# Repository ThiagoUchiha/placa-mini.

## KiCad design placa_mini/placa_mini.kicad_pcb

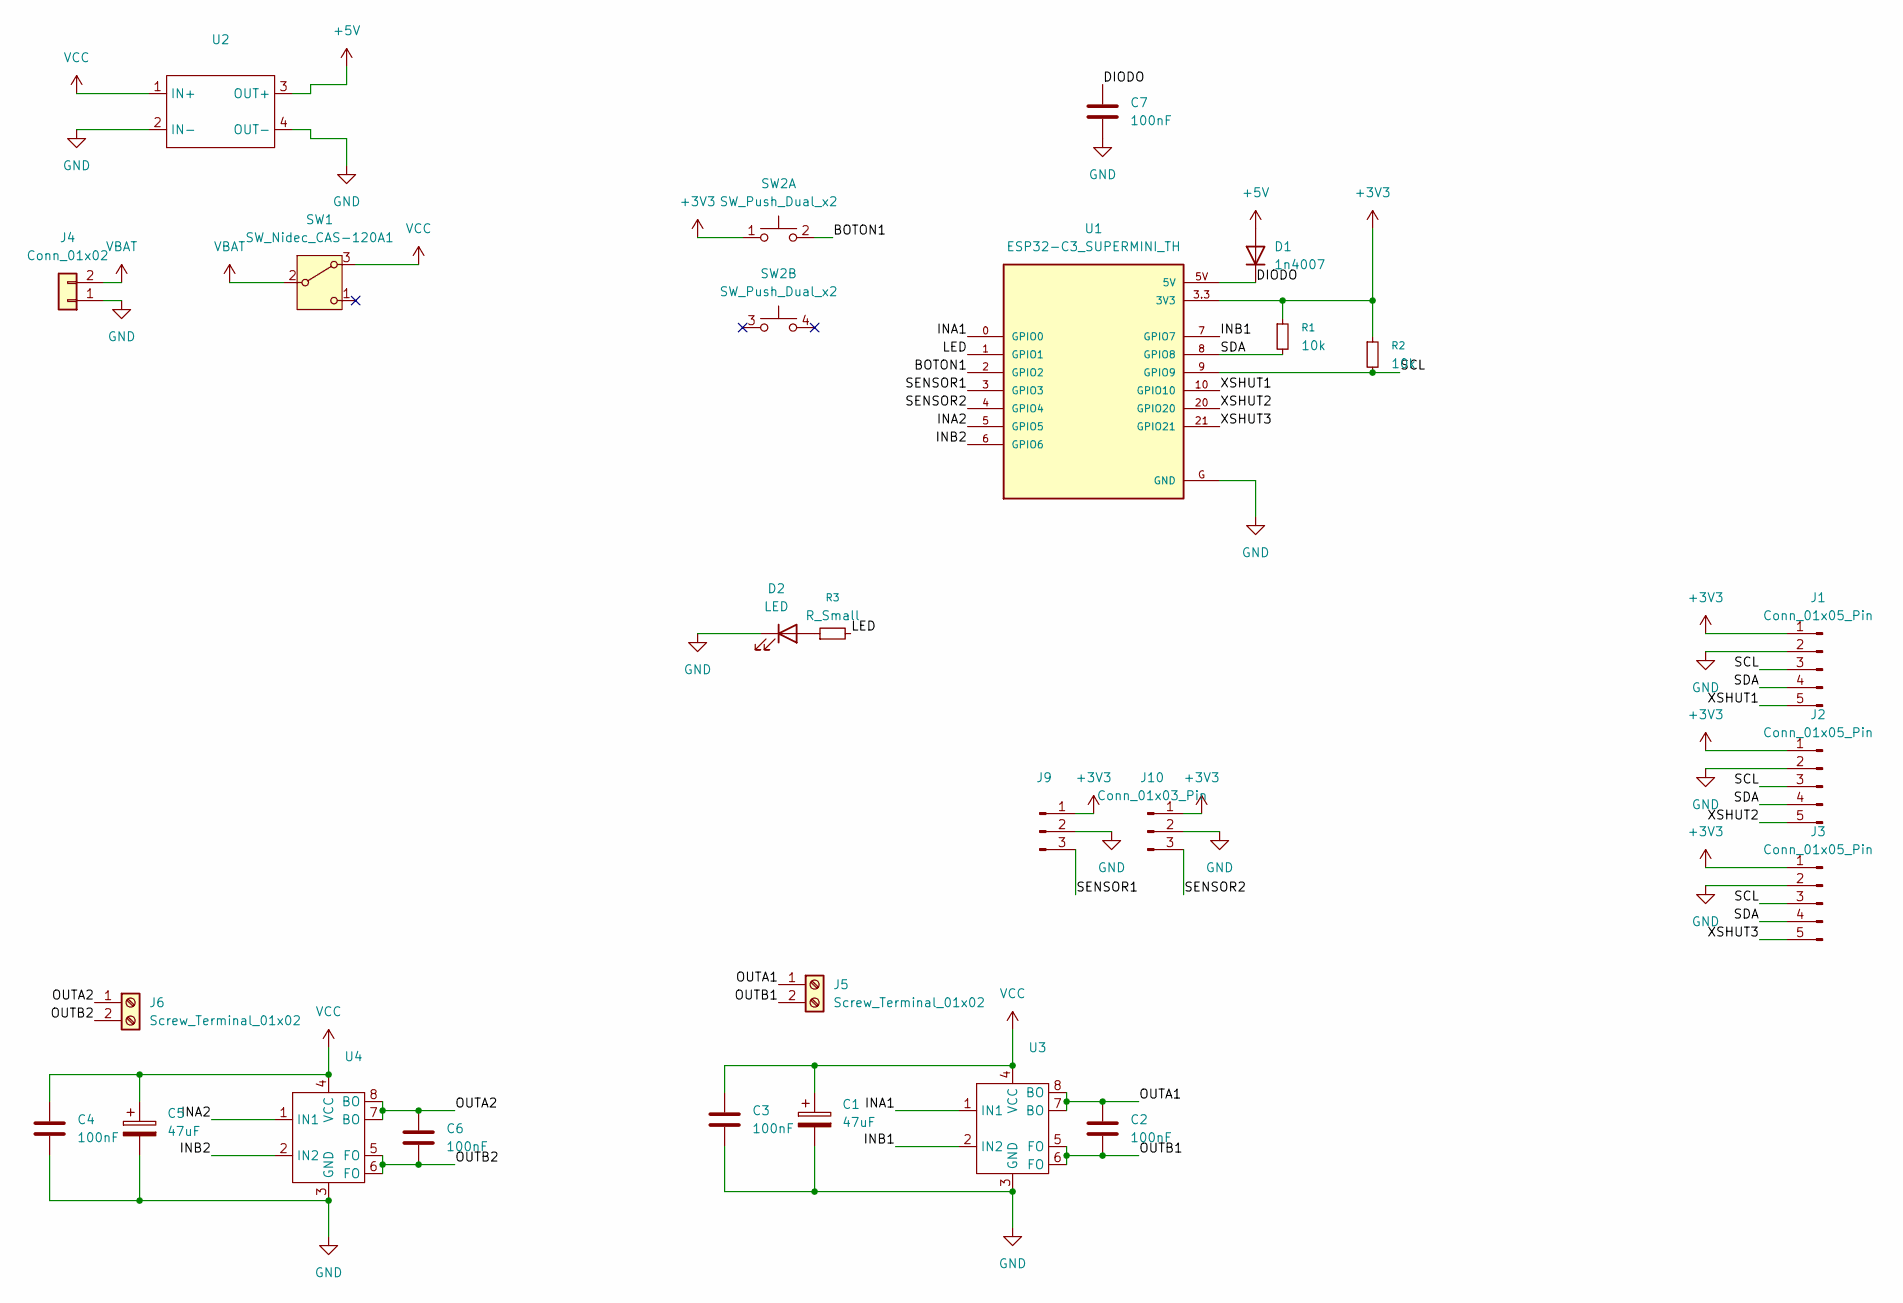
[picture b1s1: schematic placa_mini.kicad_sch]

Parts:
C1, C5: 47uF; CP_Radial_D8.0mm_P2.50mm
C2, C3, C4, C6, C7: 100nF; C_0805_2012Metric_Pad1.18x1.45mm_HandSolder
D1: 1n4007; D_A-405_P12.70mm_Horizontal
D2: LED; LED_D3.0mm
J1, J2, J3: Conn_01x05_Pin; PinHeader_1x05_P2.54mm_Vertical
J4: Conn_01x02; XT30 connector
J5, J6: Screw_Terminal_01x02; JST_XH_S2B-XH-A_1x02_P2.50mm_Horizontal
J9, J10: Conn_01x03_Pin; PinSocket_1x03_P2.54mm_Vertical
R1, R2: 10k; R_Axial_DIN0204_L3.6mm_D1.6mm_P7.62mm_Horizontal
R3: R_Small; R_0805_2012Metric_Pad1.20x1.40mm_HandSolder
SW1: SW_Nidec_CAS-120A1; PinHeader_1x03_P2.54mm_Vertical
SW2: SW_Push_Dual_x2; SW_TH_Tactile_Omron_B3F-102x
U1: ESP32-C3_SUPERMINI_TH; MODULE_ESP32-C3_SUPERMINI
U2: Mini360
U3, U4: DIP-8_W7.62mm_LongPads

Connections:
+3V3: J1.1, J2.1, J3.1, J9.1, J10.1, R1.1, R2.1, SW2.1 (C), U1.3.3 (3V3)
+5V: D1.2 (A), U2.3 (OUT+)
/BOTON1: SW2.2 (D), U1.2 (GPIO2)
/DIODO: C7.2, D1.1 (K), U1.5V
/INA1: U1.0 (GPIO0), U3.1 (IN1)
/INA2: U1.5 (GPIO5), U4.1 (IN1)
/INB1: U1.7 (GPIO7), U3.2 (IN2)
/INB2: U1.6 (GPIO6), U4.2 (IN2)
/LED: R3.2, U1.1 (GPIO1)
/OUTA1: C2.1, J5.1, U3.7 (BO), U3.8 (BO)
/OUTA2: C6.1, J6.1, U4.7 (BO), U4.8 (BO)
/OUTB1: C2.2, J5.2, U3.5 (FO), U3.6 (FO)
/OUTB2: C6.2, J6.2, U4.5 (FO), U4.6 (FO)
/SCL: J1.3, J2.3, J3.3, R2.2, U1.9 (GPIO9)
/SDA: J1.4, J2.4, J3.4, R1.2, U1.8 (GPIO8)
/SENSOR1: J9.3, U1.3 (GPIO3)
/SENSOR2: J10.3, U1.4 (GPIO4)
/XSHUT1: J1.5, U1.10 (GPIO10)
/XSHUT2: J2.5, U1.20 (GPIO20)
/XSHUT3: J3.5, U1.21 (GPIO21)
GND: C1.2, C3.2, C4.2, C5.2, C7.1, D2.1 (K), J1.2, J2.2, J3.2, J4.1, J9.2, J10.2, U1.G (GND), U2.2 (IN-), U2.4 (OUT-), U3.3 (GND), U4.3 (GND)
unnamed: D2.2 (A), R3.1
VBAT: J4.2, SW1.2 (B)
VCC: C1.1, C3.1, C4.1, C5.1, SW1.3 (A), U2.1 (IN+), U3.4 (VCC), U4.4 (VCC)

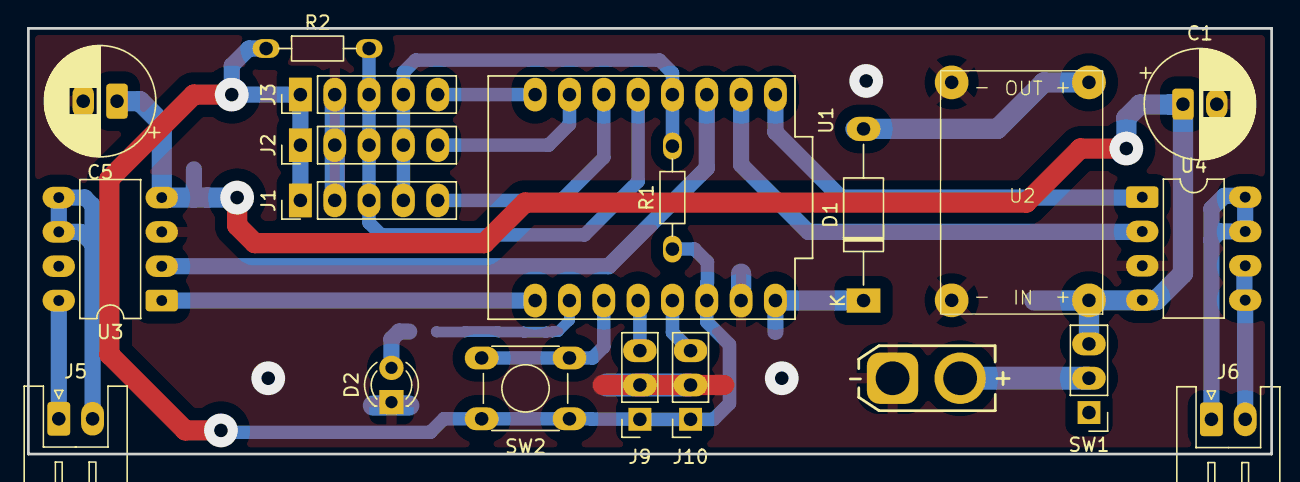
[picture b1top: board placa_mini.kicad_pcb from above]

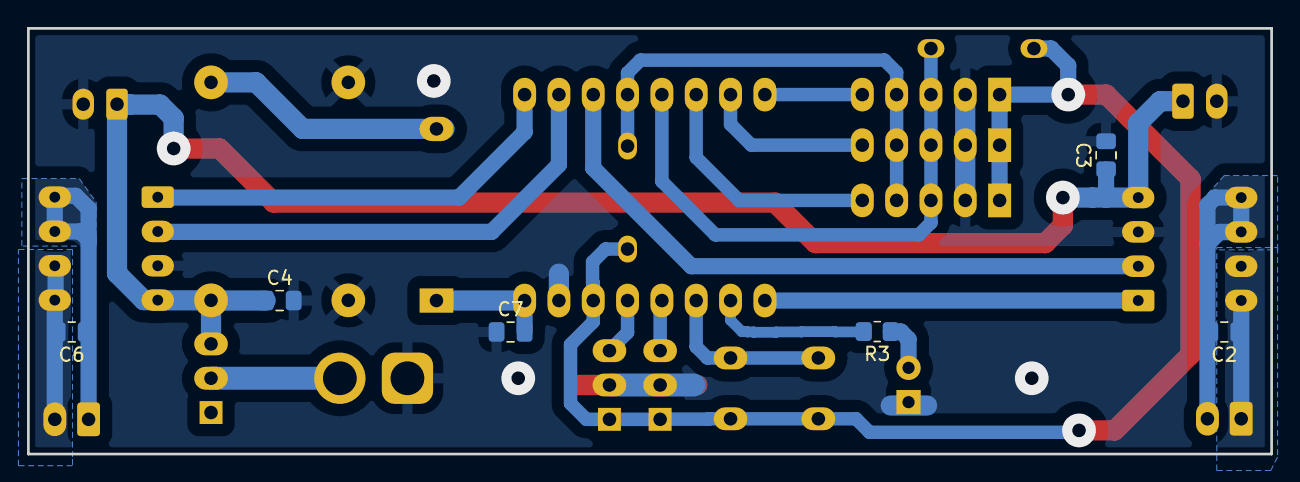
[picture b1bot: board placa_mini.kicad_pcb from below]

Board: 2 copper layers, 92.0 x 31.5 mm, 26 parts (6 on the bottom side), 24 nets.
